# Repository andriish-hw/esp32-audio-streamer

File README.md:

# Dual-ESP32 Modular Audio Streamer

A custom desktop audio streamer featuring a **dual-ESP32 architecture** designed for high reliability, dedicated audio processing, and low-latency hardware control.

---

## 🛠 System Architecture

The project splits functionality across two ESP32 microcontrollers to ensure stability and clean resource allocation:

1. **Main Controller & Bluetooth Receiver (Custom Firmware in `firmware/`):**
   * Implements high-quality Bluetooth A2DP audio sink based on the [esp32-a2dp-sink] with extra codecs (https://github.com/cfint/esp32-a2dp-sink/tree/v5.1) architecture.
   * Handles user controls, audio routing, and display output.
   * Uses the ESP32 hardware **Pulse Counter (PCNT)** peripheral for responsive, zero-lag rotary encoder handling without polling overhead.

2. **Dedicated Web-Radio Module:**
   * Powered by a secondary ESP32 running the proven [Ka-Radio32](https://github.com/karawin/Ka-Radio32) firmware as a dedicated network audio source.
   * Offloads Wi-Fi streaming, network stack management, and web-stream decoding to prevent buffer underruns and core exhaustion on the main system.
   * Communicates with main controller using UART commands.

---

## ⚡ Key Hardware & Firmware Features

* **Digital Audio Routing:** High-resolution I2S output directly to external DAC/amplifier stages.
* **Modular Hardware (KiCad):**
  * Custom mainboard with power management and signal routing.
  * Dedicated front-panel control and display breakout boards.
  * Audio level meter module.
* **Hardware-Accelerated Input:** Native hardware counter (PCNT) integration for smooth volume/menu navigation.
* **Custom Character Handling:** Custom C/C++ routines for Cyrillic metadata decoding and clean display rendering.

---

## 📁 Repository Structure

```text
├── firmware/         # Custom ESP-IDF / C++ firmware for the primary ESP32
├── hardware/         # KiCad schematics, PCB layouts, and component footprints
└── docs/             # Hardware documentation, block diagrams, and photos
---
*Note: The hardware is currently in final assembly and enclosure integration. Full schematic exports (PDF) and device photos will be added.*

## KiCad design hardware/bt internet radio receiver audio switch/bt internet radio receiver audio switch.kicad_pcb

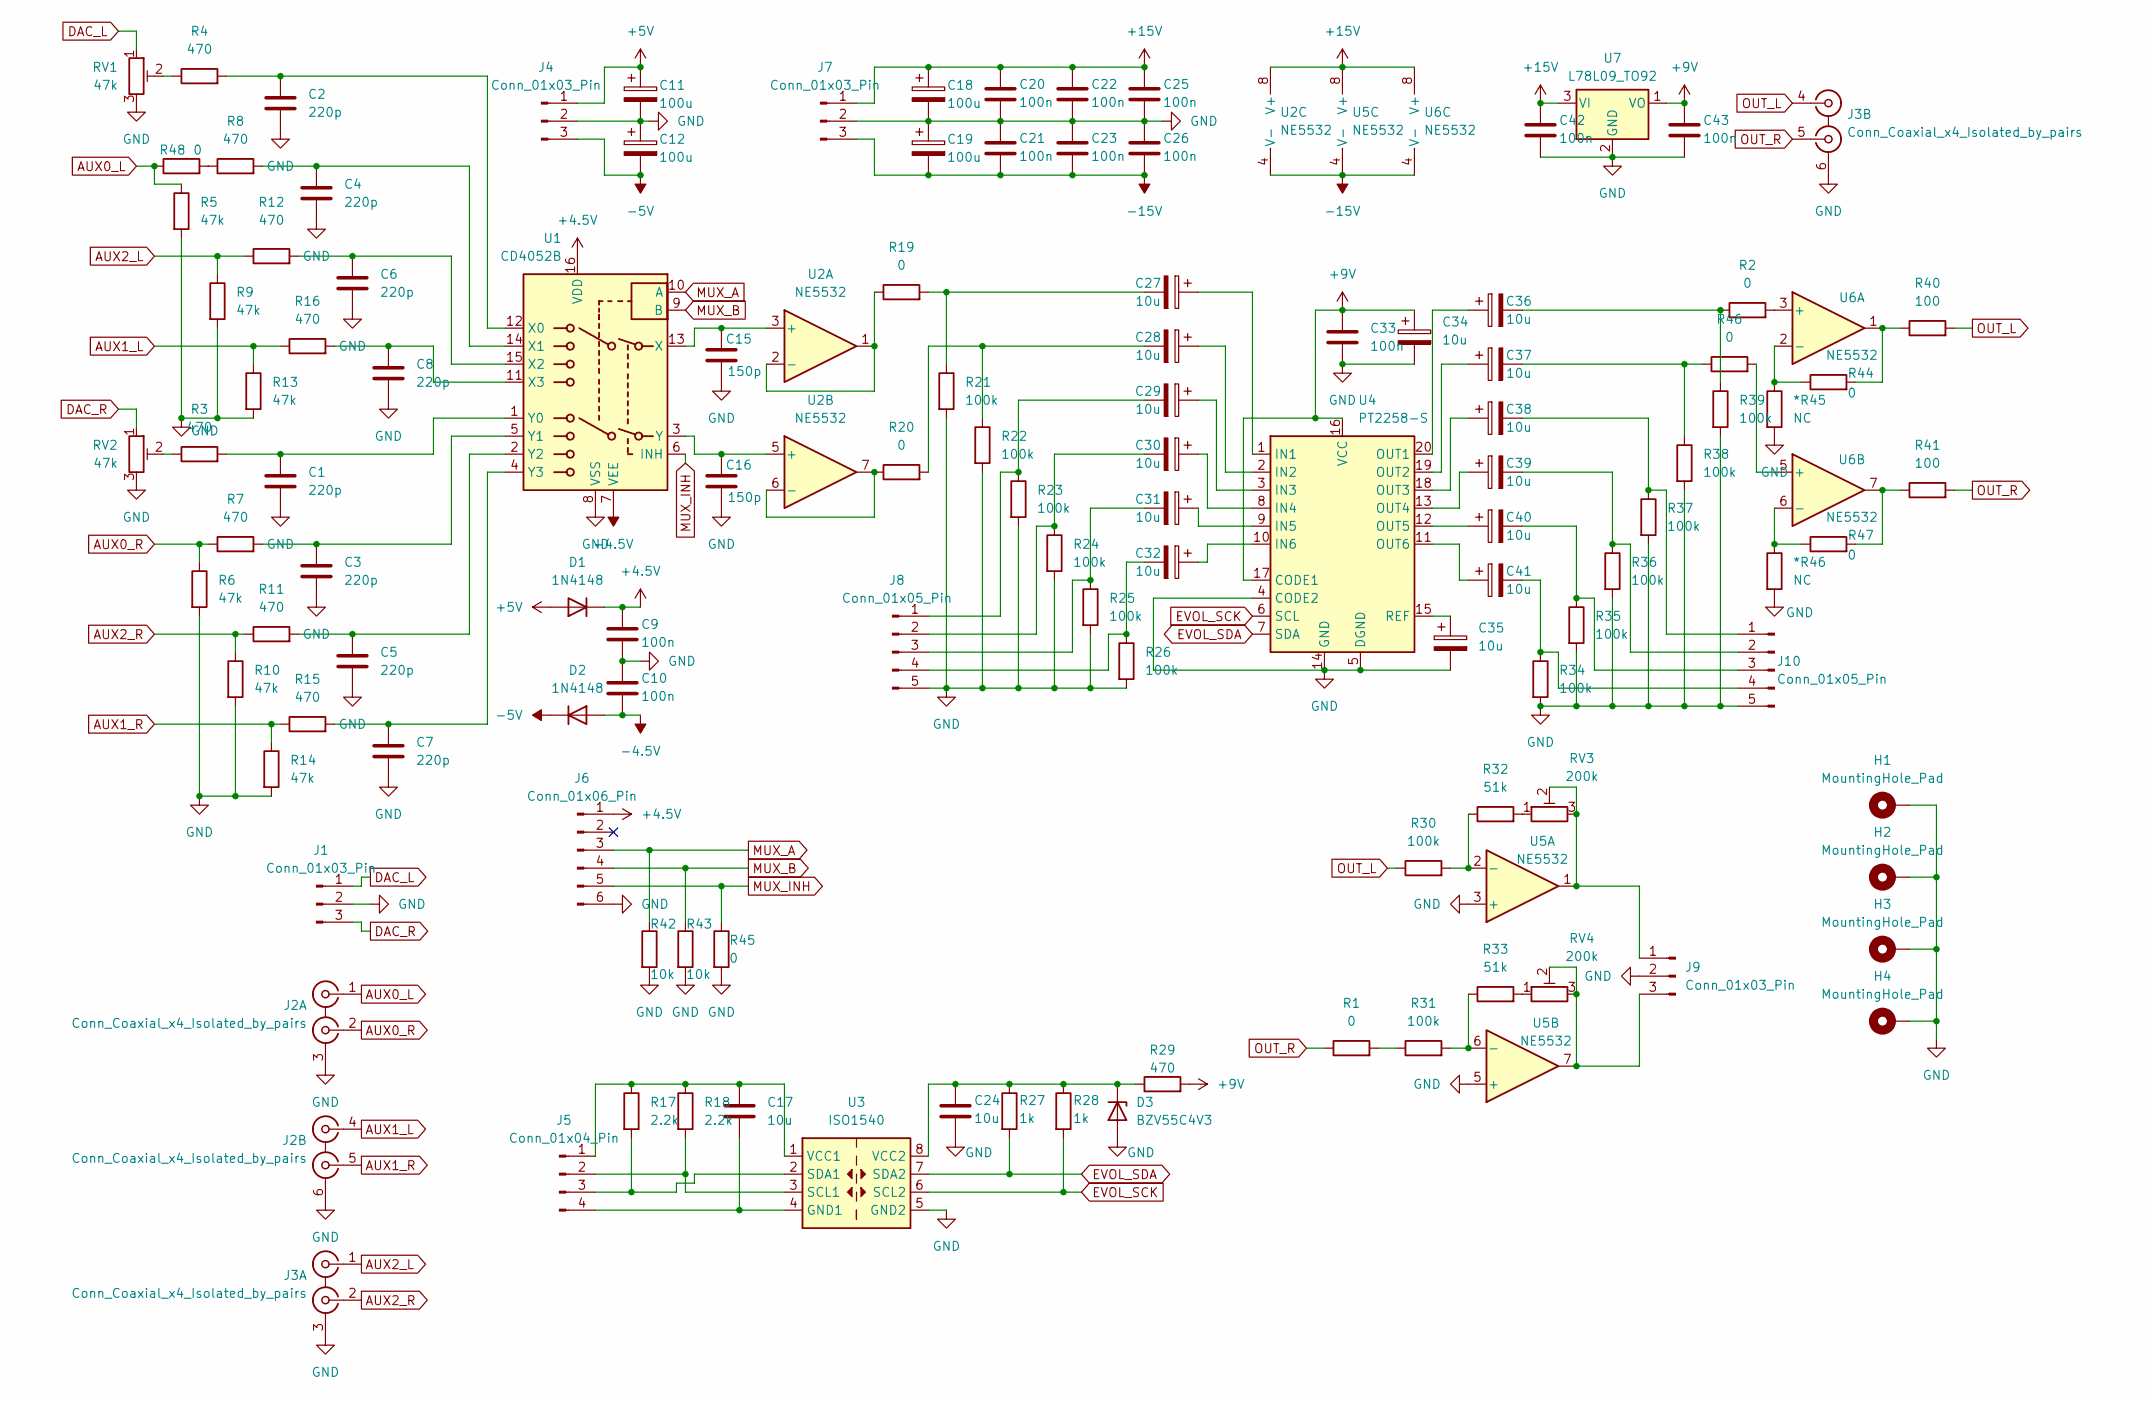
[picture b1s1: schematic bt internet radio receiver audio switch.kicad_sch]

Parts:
*R45, *R46: NC; R_0805_2012Metric_Pad1.20x1.40mm_HandSolder
C1, C2, C3, C4, C5, C6, C7, C8: 220p; C_0805_2012Metric_Pad1.18x1.45mm_HandSolder
C9, C10, C20, C21, C22, C23, C25, C26, C33, C42, C43: 100n; C_0805_2012Metric_Pad1.18x1.45mm_HandSolder
C11, C12, C18, C19: 100u; CP_Radial_D6.3mm_P2.50mm
C15, C16: 150p; C_0805_2012Metric_Pad1.18x1.45mm_HandSolder
C17, C24: 10u; C_1206_3216Metric_Pad1.33x1.80mm_HandSolder
C27, C28, C29, C30, C31, C32, C34, C35, C36, C37, C38, C39, C40, C41: 10u; CP_Radial_D5.0mm_P2.00mm
D1, D2: 1N4148; D_SOD-323_HandSoldering
D3: BZV55C4V3; D_MiniMELF
H1, H2, H3, H4: MountingHole_Pad; MountingHole_3.2mm_M3_DIN965_Pad_TopBottom
J1, J4, J7, J9: Conn_01x03_Pin; PinHeader_1x03_P2.54mm_Vertical
J2, J3: Conn_Coaxial_x4_Isolated_by_pairs; KLS1-RCA-410
J5: Conn_01x04_Pin; PinHeader_1x04_P2.54mm_Vertical
J6: Conn_01x06_Pin; PinHeader_1x06_P2.54mm_Vertical
J8, J10: Conn_01x05_Pin; PinHeader_1x05_P2.54mm_Vertical
R1, R19, R20, R44, R45, R47, R48: 0; R_0805_2012Metric_Pad1.20x1.40mm_HandSolder
R2, R46: 0; R_1206_3216Metric_Pad1.30x1.75mm_HandSolder
R3, R4, R7, R8, R11, R12, R15, R16: 470; R_0805_2012Metric_Pad1.20x1.40mm_HandSolder
R5, R6, R9, R10, R13, R14: 47k; R_0805_2012Metric_Pad1.20x1.40mm_HandSolder
R17, R18: 2.2k; R_0805_2012Metric_Pad1.20x1.40mm_HandSolder
R21, R22, R23, R24, R25, R26, R30, R31, R34, R35, R36, R37, R38, R39: 100k; R_0805_2012Metric_Pad1.20x1.40mm_HandSolder
R27, R28: 1k; R_0805_2012Metric_Pad1.20x1.40mm_HandSolder
R29: 470; R_1206_3216Metric_Pad1.30x1.75mm_HandSolder
R32, R33: 51k; R_0805_2012Metric_Pad1.20x1.40mm_HandSolder
R40, R41: 100; R_0805_2012Metric_Pad1.20x1.40mm_HandSolder
R42, R43: 10k; R_0805_2012Metric_Pad1.20x1.40mm_HandSolder
RV1, RV2: 47k; Potentiometer_Runtron_RM-065_Vertical
RV3, RV4: 200k; Potentiometer_Runtron_RM-065_Vertical
U1: CD4052B; SOIC-16_3.9x9.9mm_P1.27mm
U2, U5, U6: NE5532; DIP-8_W7.62mm_Socket_LongPads
U3: ISO1540; SOIC-8_3.9x4.9mm_P1.27mm
U4: PT2258-S; SO-20_12.8x7.5mm_P1.27mm
U7: L78L09_TO92; TO-92_Inline_Wide

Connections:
+4.5V: C9.1, D1.1 (K), J6.1, U1.16 (VDD)
+5V: C11.1, D1.2 (A), J4.1
+9V: C33.1, C34.1, C43.1, R29.2, U4.16 (VCC), U4.17 (CODE1), U7.1 (VO)
+15V: C18.1, C20.1, C22.1, C25.1, C42.1, J7.1, U2.8 (V+), U5.8 (V+), U6.8 (V+), U7.3 (VI)
-4.5V: C10.2, D2.2 (A), U1.7 (VEE)
-5V: C12.2, D2.1 (K), J4.3
-15V: C19.2, C21.2, C23.2, C26.2, J7.3, U2.4 (V-), U5.4 (V-), U6.4 (V-)
AUX0_L: J2.1 (IN1), R5.1, R48.1
AUX0_R: J2.2 (IN2), R6.1, R7.1
AUX1_L: J2.4 (IN1), R13.1, R16.1
AUX1_R: J2.5 (IN2), R14.1, R15.1
AUX2_L: J3.1 (IN1), R9.1, R12.1
AUX2_R: J3.2 (IN2), R10.1, R11.1
DAC_L: J1.1, RV1.1
DAC_R: J1.3, RV2.1
EVOL_SCK: R28.2, U3.6 (SCL2), U4.6 (SCL)
EVOL_SDA: R27.2, U3.7 (SDA2), U4.7 (SDA)
GND: *R45.2, *R46.2, C1.2, C2.2, C3.2, C4.2, C5.2, C6.2, C7.2, C8.2, C9.2, C10.1, C11.2, C12.1, C15.2, C16.2, C18.2, C19.1, C20.2, C21.1, C22.2, C23.1, C24.2, C25.2, C26.1, C33.2, C34.2, C35.2, C42.2, C43.2, D3.2 (A), H1.1, H2.1, H3.1, H4.1, J1.2, J2.3 (EXT), J2.6 (EXT), J3.3 (EXT), J3.6 (EXT), J4.2, J6.6, J7.2, J8.5, J9.2, J10.5, R5.2, R6.2, R9.2, R10.2, R13.2, R14.2, R21.2, R22.2, R23.2, R24.2, R25.2, R26.2, R34.2, R35.2, R36.2, R37.2, R38.2, R39.2, R42.2, R43.2, R45.2, RV1.3, RV2.3, U1.8 (VSS), U3.5 (GND2), U4.4 (CODE2), U4.5 (DGND), U4.14 (GND), U5.3 (+), U5.5 (+), U7.2 (GND)
MUX_A: J6.3, R42.1, U1.10 (A)
MUX_B: J6.4, R43.1, U1.9 (B)
MUX_INH: J6.5, R45.1, U1.6 (INH)
unnamed: C27.2, R19.2, R21.1
unnamed: C28.2, R20.2, R22.1
unnamed: C36.2, R2.1, R39.1
unnamed: C37.2, R38.1, R46.1
unnamed: C24.1, D3.1 (K), R27.1, R28.1, R29.1, U3.8 (VCC2)
unnamed: C17.1, J5.1, R17.1, R18.1, U3.1 (VCC1)
unnamed: J5.2, R18.2, U3.3 (SCL1)
unnamed: J5.3, R17.2, U3.2 (SDA1)
unnamed: C17.2, J5.4, U3.4 (GND1)
unnamed: C29.2, J8.1, R23.1
unnamed: C30.2, J8.2, R24.1
unnamed: C31.2, J8.3, R25.1
unnamed: C32.2, J8.4, R26.1
unnamed: J9.1, RV3.2, RV3.3, U5.1
unnamed: J9.3, RV4.2, RV4.3, U5.7
unnamed: C38.2, J10.1, R37.1
unnamed: C39.2, J10.2, R36.1
unnamed: C40.2, J10.3, R35.1
unnamed: C41.2, J10.4, R34.1
unnamed: R1.2, R31.1
unnamed: R3.1, RV2.2
unnamed: R4.1, RV1.2
unnamed: R32.2, RV3.1
unnamed: R33.2, RV4.1
unnamed: R40.1, R44.2, U6.1
unnamed: R41.1, R47.2, U6.7
unnamed: R8.1, R48.2
unnamed: C2.1, R4.2, U1.12 (X0)
unnamed: C4.1, R8.2, U1.14 (X1)
unnamed: C6.1, R12.2, U1.15 (X2)
unnamed: C8.1, R16.2, U1.11 (X3)
unnamed: C15.1, U1.13 (X), U2.3 (+)
unnamed: C1.1, R3.2, U1.1 (Y0)
unnamed: C3.1, R7.2, U1.5 (Y1)
unnamed: C5.1, R11.2, U1.2 (Y2)
unnamed: C7.1, R15.2, U1.4 (Y3)
unnamed: C16.1, U1.3 (Y), U2.5 (+)
unnamed: R19.1, U2.1, U2.2 (-)
unnamed: R20.1, U2.6 (-), U2.7
unnamed: C27.1, U4.1 (IN1)
unnamed: C28.1, U4.2 (IN2)
unnamed: C29.1, U4.3 (IN3)
unnamed: C30.1, U4.8 (IN4)
unnamed: C31.1, U4.9 (IN5)
unnamed: C32.1, U4.10 (IN6)
unnamed: C36.1, U4.20 (OUT1)
unnamed: C37.1, U4.19 (OUT2)
unnamed: C38.1, U4.18 (OUT3)
unnamed: C39.1, U4.13 (OUT4)
unnamed: C40.1, U4.12 (OUT5)
unnamed: C41.1, U4.11 (OUT6)
unnamed: C35.1, U4.15 (REF)
unnamed: R30.2, R32.1, U5.2 (-)
unnamed: R31.2, R33.1, U5.6 (-)
unnamed: R2.2, U6.3 (+)
unnamed: *R45.1, R44.1, U6.2 (-)
unnamed: R46.2, U6.5 (+)
unnamed: *R46.1, R47.1, U6.6 (-)
OUT_L: J3.4 (IN1), R30.1, R40.2
OUT_R: J3.5 (IN2), R1.1, R41.2

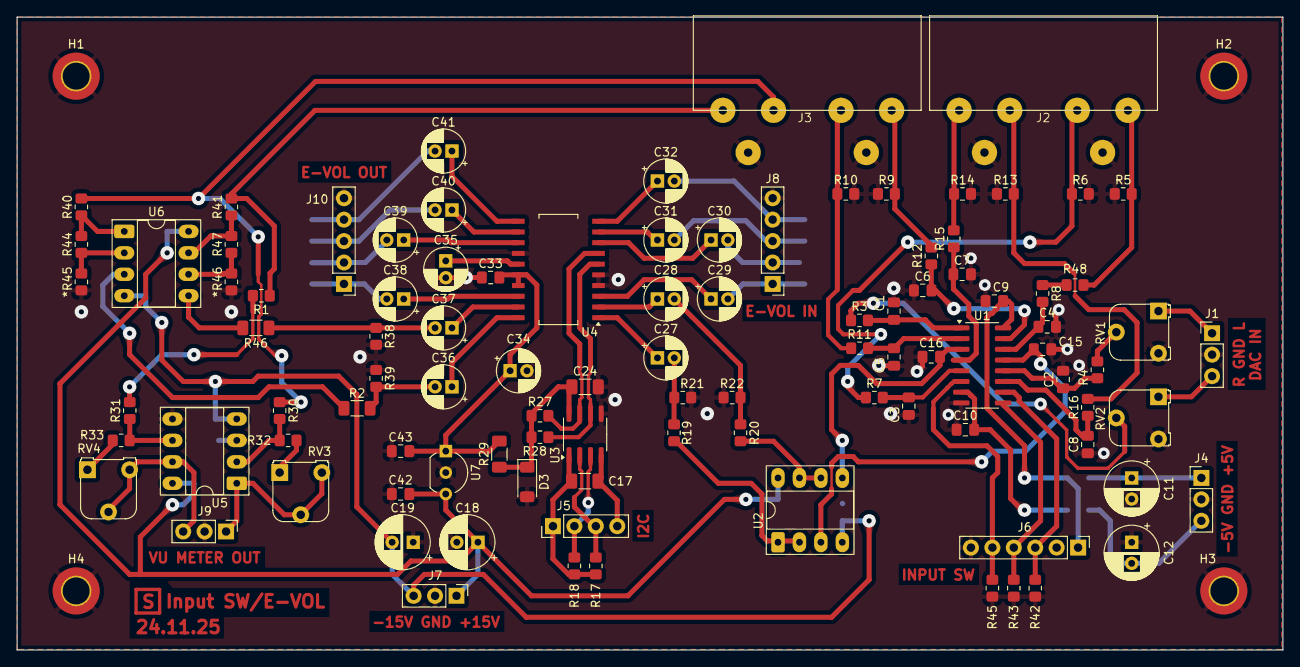
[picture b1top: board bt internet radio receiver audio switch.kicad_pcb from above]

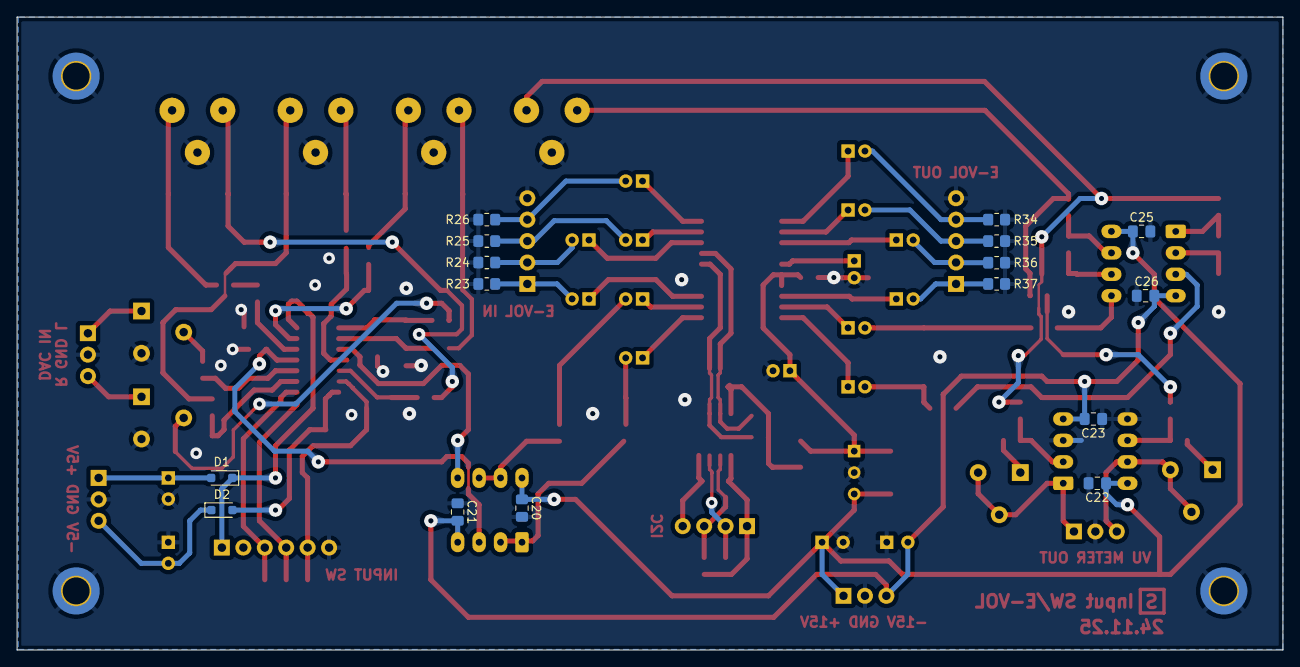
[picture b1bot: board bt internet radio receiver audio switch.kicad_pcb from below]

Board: 2 copper layers, 150.0 x 75.0 mm, 119 parts (16 on the bottom side), 81 nets.

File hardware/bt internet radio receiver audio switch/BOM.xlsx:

Reference | Qty | Value | DNP | Exclude from BOM | Exclude from Board | Footprint | Datasheet
*R45,*R46 | 2 | NC | 1 |  |  | Resistor_SMD:R_0805_2012Metric_Pad1.20x1.40mm_HandSolder | ~
C1,C2,C3,C4,C5,C6,C7,C8 | 8 | 220p | 1 |  |  | Capacitor_SMD:C_0805_2012Metric_Pad1.18x1.45mm_HandSolder | ~
C9,C10,C20,C21,C22,C23,C25,C26,C33,C42,C43 | 11 | 100n | 0 |  |  | Capacitor_SMD:C_0805_2012Metric_Pad1.18x1.45mm_HandSolder | ~
C11,C12,C18,C19 | 4 | 100u | 0 |  |  | Capacitor_THT:CP_Radial_D6.3mm_P2.50mm | ~
C15,C16 | 2 | 150p | 1 |  |  | Capacitor_SMD:C_0805_2012Metric_Pad1.18x1.45mm_HandSolder | ~
C17,C24 | 2 | 10u | 0 |  |  | Capacitor_SMD:C_1206_3216Metric_Pad1.33x1.80mm_HandSolder | ~
C27,C28,C29,C30,C31,C32,C34,C35,C36,C37,C38,C39,C40,C41 | 14 | 10u | 0 |  |  | Capacitor_THT:CP_Radial_D5.0mm_P2.00mm | ~
D1,D2 | 2 | 1N4148 | 0 |  |  | Diode_SMD:D_SOD-323_HandSoldering | https://assets.nexperia.com/documents/data-sheet/1N4148_1N4448.pdf
D3 | 1 | BZV55C4V3 | 1 |  |  | Diode_SMD:D_MiniMELF | https://assets.nexperia.com/documents/data-sheet/BZV55_SER.pdf
J1,J4,J7,J9 | 4 | Conn_01x03_Pin | 0 |  |  | Connector_PinHeader_2.54mm:PinHeader_1x03_P2.54mm_Vertical | ~
J2,J3 | 2 | Conn_Coaxial_x4_Isolated_by_pairs | 0 |  |  | Connector:KLS1-RCA-410
J5 | 1 | Conn_01x04_Pin | 0 |  |  | Connector_PinHeader_2.54mm:PinHeader_1x04_P2.54mm_Vertical | ~
J6 | 1 | Conn_01x06_Pin | 0 |  |  | Connector_PinHeader_2.54mm:PinHeader_1x06_P2.54mm_Vertical | ~
J8,J10 | 2 | Conn_01x05_Pin | 0 |  |  | Connector_PinHeader_2.54mm:PinHeader_1x05_P2.54mm_Vertical | ~
R1,R19,R20,R44,R45,R47 | 6 | 0 | 1 |  |  | Resistor_SMD:R_0805_2012Metric_Pad1.20x1.40mm_HandSolder | ~
R2,R46 | 2 | 0 | 1 |  |  | Resistor_SMD:R_1206_3216Metric_Pad1.30x1.75mm_HandSolder | ~
R3,R4,R7,R8,R11,R12,R15,R16 | 8 | 470 | 1 |  |  | Resistor_SMD:R_0805_2012Metric_Pad1.20x1.40mm_HandSolder | ~
R5,R6,R9,R10,R13,R14 | 6 | 47k | 1 |  |  | Resistor_SMD:R_0805_2012Metric_Pad1.20x1.40mm_HandSolder | ~
R17,R18 | 2 | 2.2k | 0 |  |  | Resistor_SMD:R_0805_2012Metric_Pad1.20x1.40mm_HandSolder | ~
R21,R22,R23,R24,R25,R26,R30,R31,R34,R35,R36,R37,R38,R39 | 14 | 100k | 0 |  |  | Resistor_SMD:R_0805_2012Metric_Pad1.20x1.40mm_HandSolder | ~
R27,R28 | 2 | 1k | 0 |  |  | Resistor_SMD:R_0805_2012Metric_Pad1.20x1.40mm_HandSolder | ~
R29 | 1 | 470 | 1 |  |  | Resistor_SMD:R_1206_3216Metric_Pad1.30x1.75mm_HandSolder | ~
R32,R33 | 2 | 51k | 0 |  |  | Resistor_SMD:R_0805_2012Metric_Pad1.20x1.40mm_HandSolder | ~
R40,R41 | 2 | 100 | 1 |  |  | Resistor_SMD:R_0805_2012Metric_Pad1.20x1.40mm_HandSolder | ~
R42,R43 | 2 | 10k | 1 |  |  | Resistor_SMD:R_0805_2012Metric_Pad1.20x1.40mm_HandSolder | ~
RV1,RV2 | 2 | 47k | 0 |  |  | Potentiometer_THT:Potentiometer_Runtron_RM-065_Vertical | ~
RV3,RV4 | 2 | 200k | 0 |  |  | Potentiometer_THT:Potentiometer_Runtron_RM-065_Vertical | ~
U1 | 1 | CD4052B | 1 |  |  | Package_SO:SOIC-16_3.9x9.9mm_P1.27mm | http://www.ti.com/lit/ds/symlink/cd4052b.pdf
U2,U5,U6 | 3 | NE5532 | 0 |  |  | Package_DIP:DIP-8_W7.62mm_Socket_LongPads | http://www.ti.com/lit/ds/symlink/ne5532.pdf
U3 | 1 | ISO1540 | 0 |  |  | Package_SO:SOIC-8_3.9x4.9mm_P1.27mm | http://www.ti.com/lit/ds/symlink/iso1541.pdf
U4 | 1 | PT2258-S | 0 |  |  | Package_SO:SO-20_12.8x7.5mm_P1.27mm | http://www.princeton.com.tw/Portals/0/Product/PT2258-s.pdf
U7 | 1 | L78L09_TO92 | 0 |  |  | Package_TO_SOT_THT:TO-92_Inline_Wide | http://www.st.com/content/ccc/resource/technical/document/da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
 | 114
 | 41 | 0.35964912280701755

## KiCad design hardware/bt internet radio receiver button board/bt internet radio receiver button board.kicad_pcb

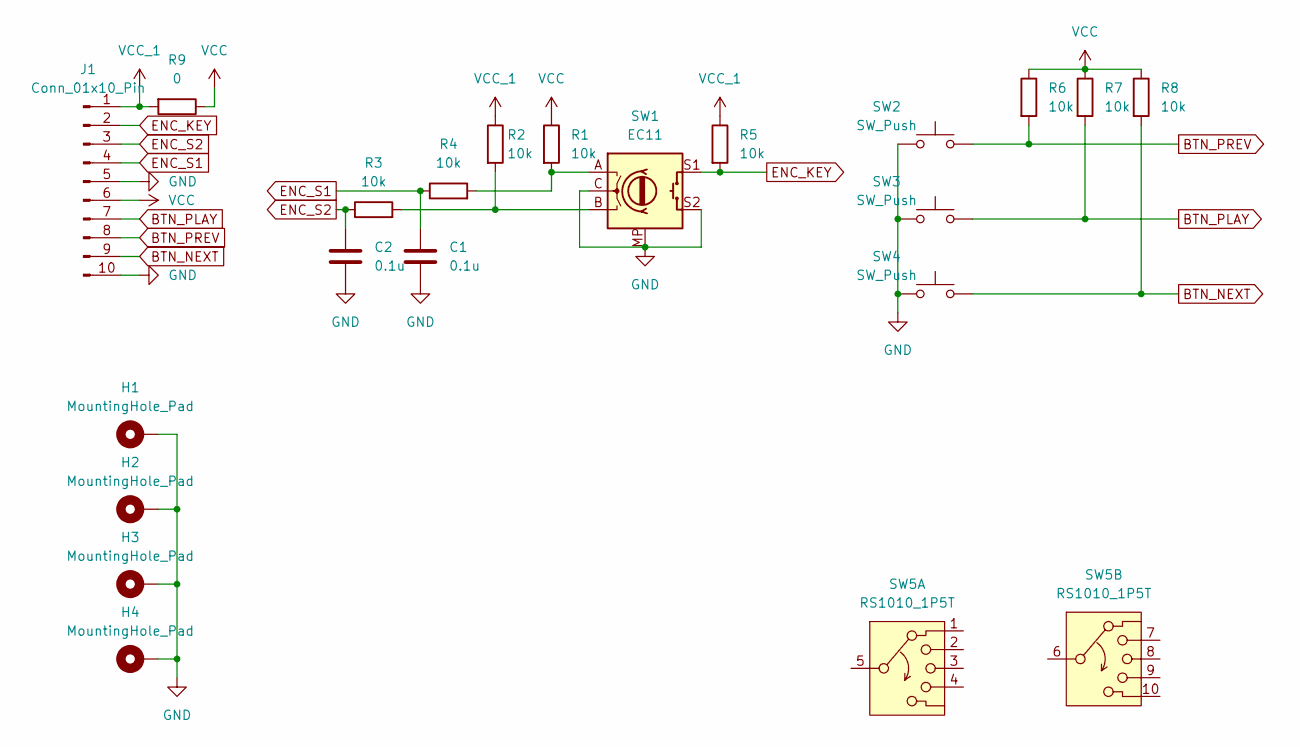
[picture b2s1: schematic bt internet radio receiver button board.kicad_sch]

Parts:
C1, C2: 0.1u; C_0805_2012Metric_Pad1.18x1.45mm_HandSolder
H1, H2, H3, H4: MountingHole_Pad; MountingHole_3.2mm_M3_Pad_TopBottom
J1: Conn_01x10_Pin; PinHeader_1x10_P2.54mm_Horizontal
R1, R2, R3, R4, R5, R6, R7, R8: 10k; R_0805_2012Metric_Pad1.20x1.40mm_HandSolder
R9: 0; R_Axial_DIN0204_L3.6mm_D1.6mm_P7.62mm_Horizontal
SW1: EC11; RotaryEncoder_Alps_EC11E-Switch_Vertical_H20mm
SW2, SW3, SW4: SW_Push; SW_PUSH_6mm
SW5: RS1010_1P5T

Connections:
BTN_NEXT: J1.9, R8.2, SW4.1
BTN_PLAY: J1.7, R7.2, SW3.1
BTN_PREV: J1.8, R6.2, SW2.1
ENC_KEY: J1.2, R5.2, SW1.S1
ENC_S1: C1.1, J1.4, R4.1
ENC_S2: C2.1, J1.3, R3.1
GND: C1.2, C2.2, H1.1, H2.1, H3.1, H4.1, J1.5, J1.10, SW1.C, SW1.MP, SW1.S2, SW2.2, SW3.2, SW4.2
unnamed: R1.2, R4.2, SW1.A
unnamed: R2.2, R3.2, SW1.B
VCC: J1.6, R1.1, R6.1, R7.1, R8.1, R9.1
VCC_1: J1.1, R2.1, R5.1, R9.2

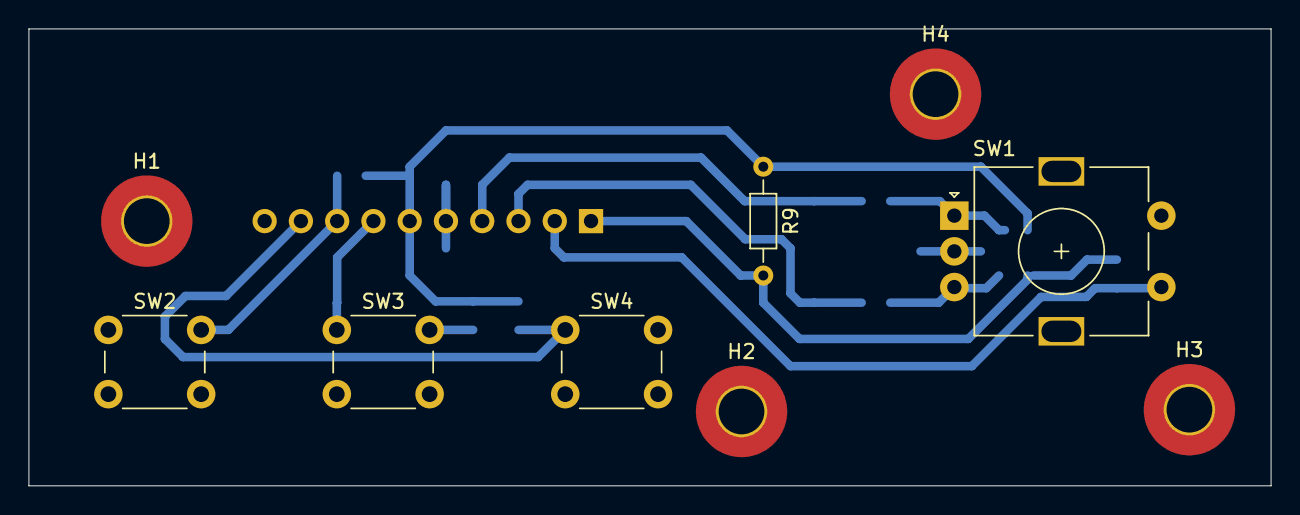
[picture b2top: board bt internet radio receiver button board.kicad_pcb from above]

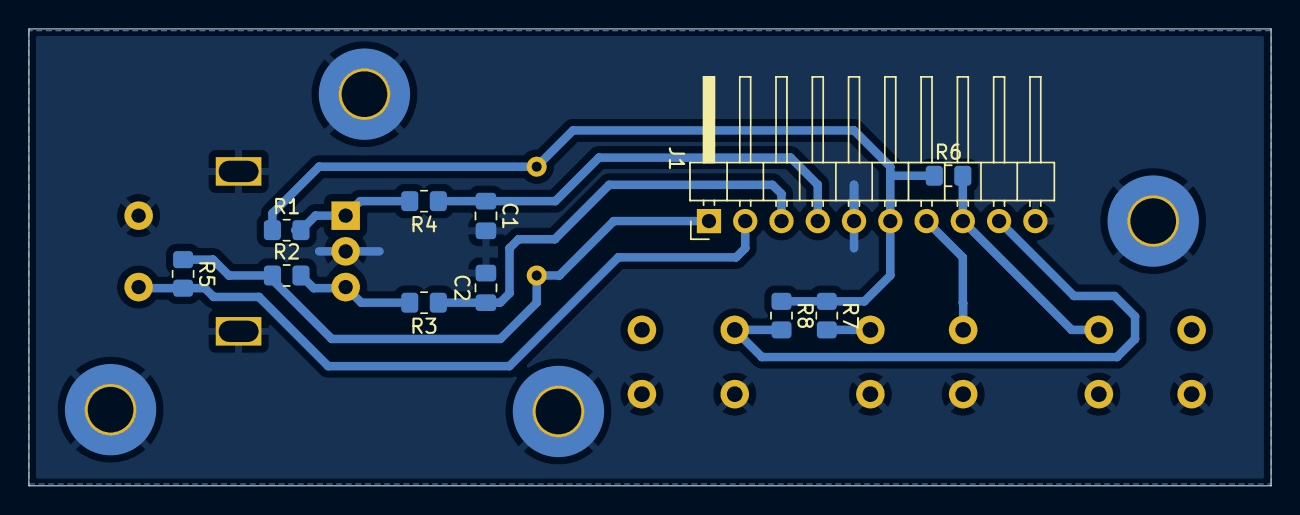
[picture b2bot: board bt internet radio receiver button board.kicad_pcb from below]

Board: 2 copper layers, 87.0 x 32.0 mm, 20 parts (11 on the bottom side), 11 nets.

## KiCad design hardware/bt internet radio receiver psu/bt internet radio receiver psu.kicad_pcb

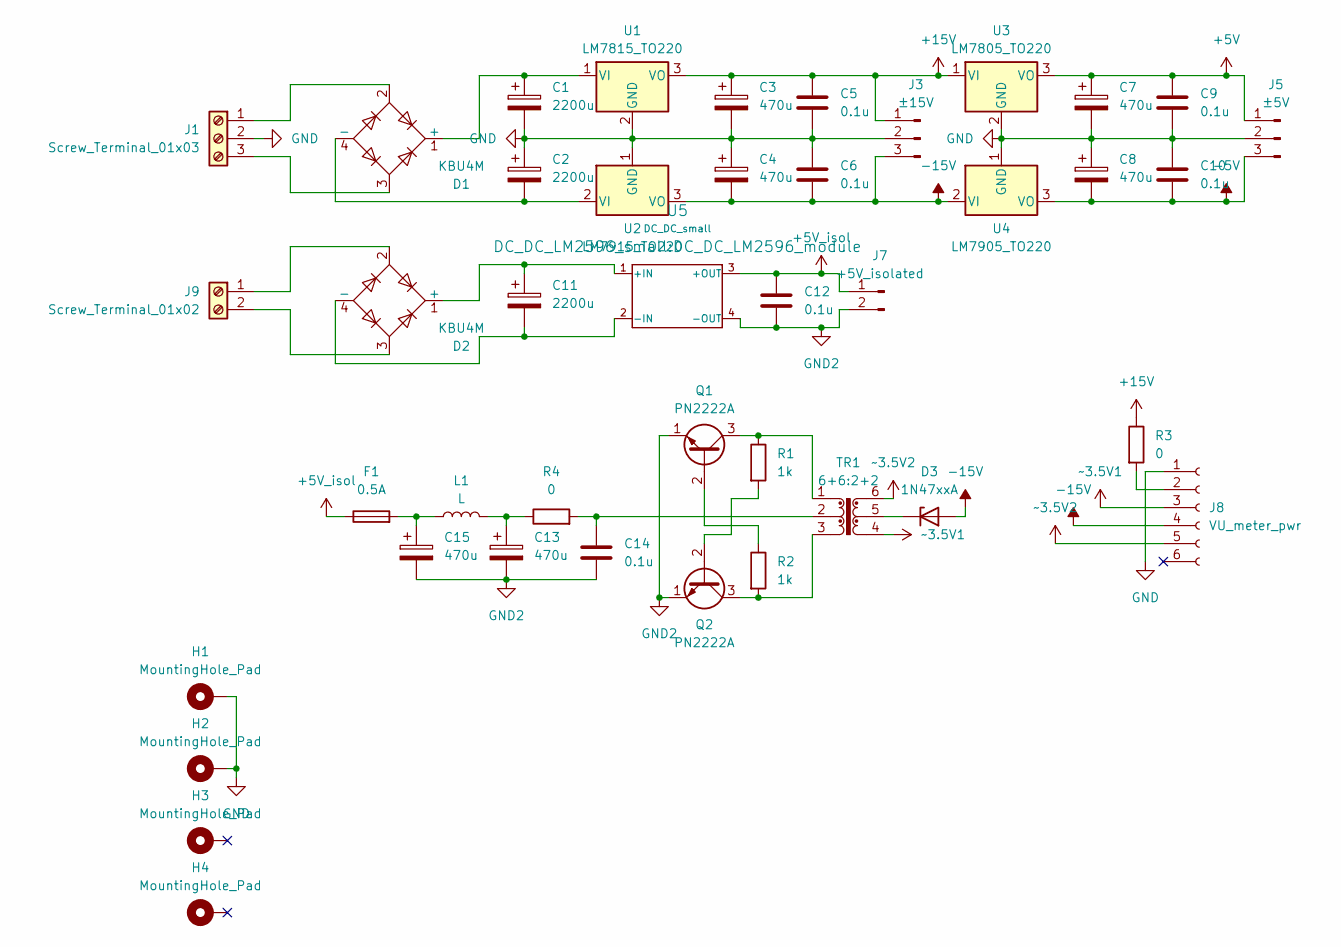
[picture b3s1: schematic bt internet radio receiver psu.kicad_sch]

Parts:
C1, C2, C11: 2200u; C_Radial_D16.0mm_H25.0mm_P7.50mm
C3, C4, C7, C8, C13, C15: 470u; C_Radial_D10.0mm_H12.5mm_P5.00mm
C5, C6, C9, C10, C12, C14: 0.1u; C_Disc_D4.7mm_W2.5mm_P5.00mm
D1, D2: KBU4M; Diode_Bridge_Vishay_KBPM
D3: 1N47xxA; D_DO-41_SOD81_P5.08mm_Vertical_KathodeUp
F1: 0.5A; Fuseholder_Clip-5x20mm_Keystone_3512_Inline_P23.62x7.27mm_D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
H1, H2, H3, H4: MountingHole_Pad; MountingHole_3.2mm_M3_DIN965_Pad_TopOnly
J1: Screw_Terminal_01x03; TerminalBlock_bornier-3_P5.08mm
J3: ±15V; PinHeader_1x03_P2.54mm_Vertical
J5: ±5V; PinHeader_1x03_P2.54mm_Vertical
J7: +5V_isolated; PinHeader_1x02_P2.54mm_Vertical
J8: VU_meter_pwr; PinSocket_1x06_P2.54mm_Vertical
J9: Screw_Terminal_01x02; TerminalBlock_bornier-2_P5.08mm
L1: L; L_Radial_D12.0mm_P6.00mm_Murata_1900R
Q1, Q2: PN2222A; TO-92_Inline_Wide
R1, R2: 1k; R_Axial_DIN0207_L6.3mm_D2.5mm_P10.16mm_Horizontal
R3: 0; R_Axial_DIN0207_L6.3mm_D2.5mm_P10.16mm_Horizontal
R4: 0; R_Axial_DIN0204_L3.6mm_D1.6mm_P7.62mm_Horizontal
TR1: 6+6:2+2; Transformer_Toroid_Tapped_D=23mm_d=13mm
U1: LM7815_TO220; TO-220-3_Vertical
U2: LM7915_TO220; TO-220-3_Vertical
U3: LM7805_TO220; TO-220-3_Vertical
U4: LM7905_TO220; TO-220-3_Vertical
U5: DC_DC_small; DC_DC_LM2596_module

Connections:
+5V: C7.1, C9.1, J5.1, U3.3 (VO)
+5V_isol: C12.1, F1.1, J7.1, U5.3 (+OUT)
+15V: C3.1, C5.1, J3.1, R3.1, U1.3 (VO), U3.1 (VI)
-5V: C8.2, C10.2, J5.3, U4.3 (VO)
-15V: C4.2, C6.2, D3.2 (A), J3.3, J8.4, U2.3 (VO), U4.2 (VI)
GND: C1.2, C2.1, C3.2, C4.1, C5.2, C6.1, C7.2, C8.1, C9.2, C10.1, H1.1, H2.1, J1.2, J3.2, J5.2, J8.1, U1.2 (GND), U2.1 (GND), U3.2 (GND), U4.1 (GND)
GND2: C12.2, C13.2, C14.2, C15.2, J7.2, Q1.1 (E), Q2.1 (E), U5.4 (-OUT)
unnamed: C13.1, L1.2, R4.1
unnamed: C14.1, R4.2, TR1.2
unnamed: C15.1, F1.2, L1.1
unnamed: C1.1, D1.1 (+), U1.1 (VI)
unnamed: C2.2, D1.4 (-), U2.2 (VI)
unnamed: C11.1, D2.1 (+), U5.1 (+IN)
unnamed: C11.2, D2.4 (-), U5.2 (-IN)
unnamed: D3.1 (K), TR1.5
unnamed: D1.2, J1.1
unnamed: D1.3, J1.3
unnamed: J8.2, R3.2
unnamed: D2.2, J9.1
unnamed: D2.3, J9.2
unnamed: Q1.2 (B), R2.1
unnamed: Q1.3 (C), R1.1, TR1.1
unnamed: Q2.2 (B), R1.2
unnamed: Q2.3 (C), R2.2, TR1.3
~3.5V1: J8.3, TR1.4
~3.5V2: J8.5, TR1.6

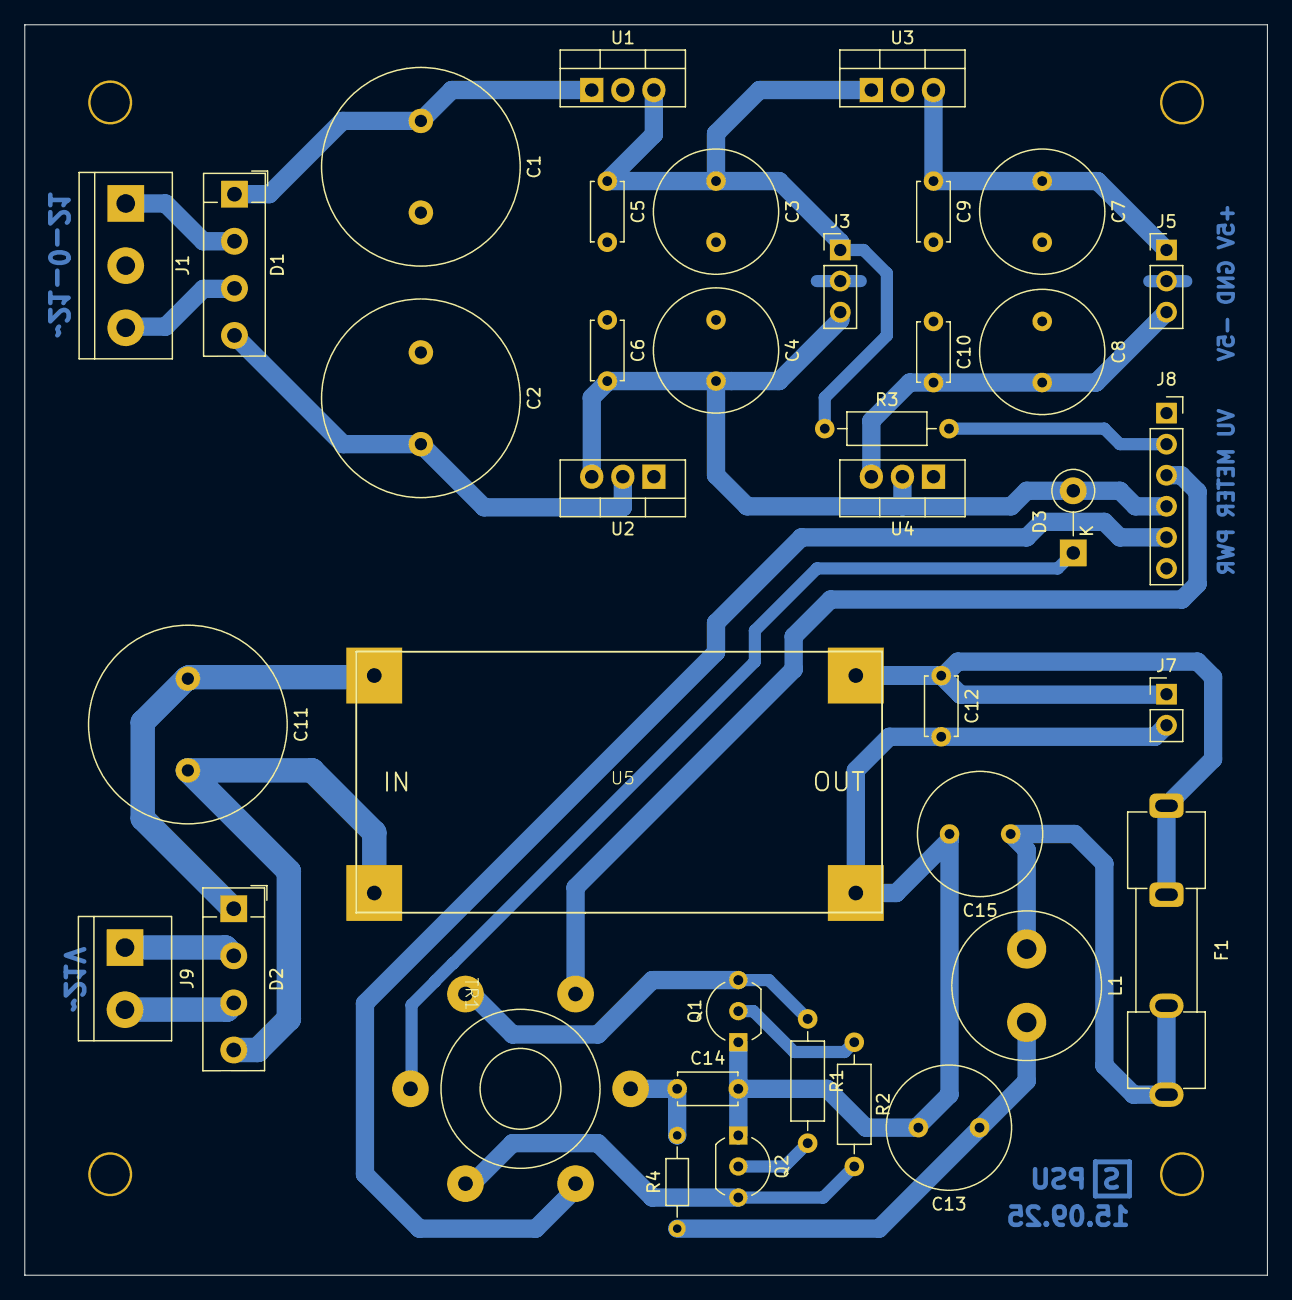
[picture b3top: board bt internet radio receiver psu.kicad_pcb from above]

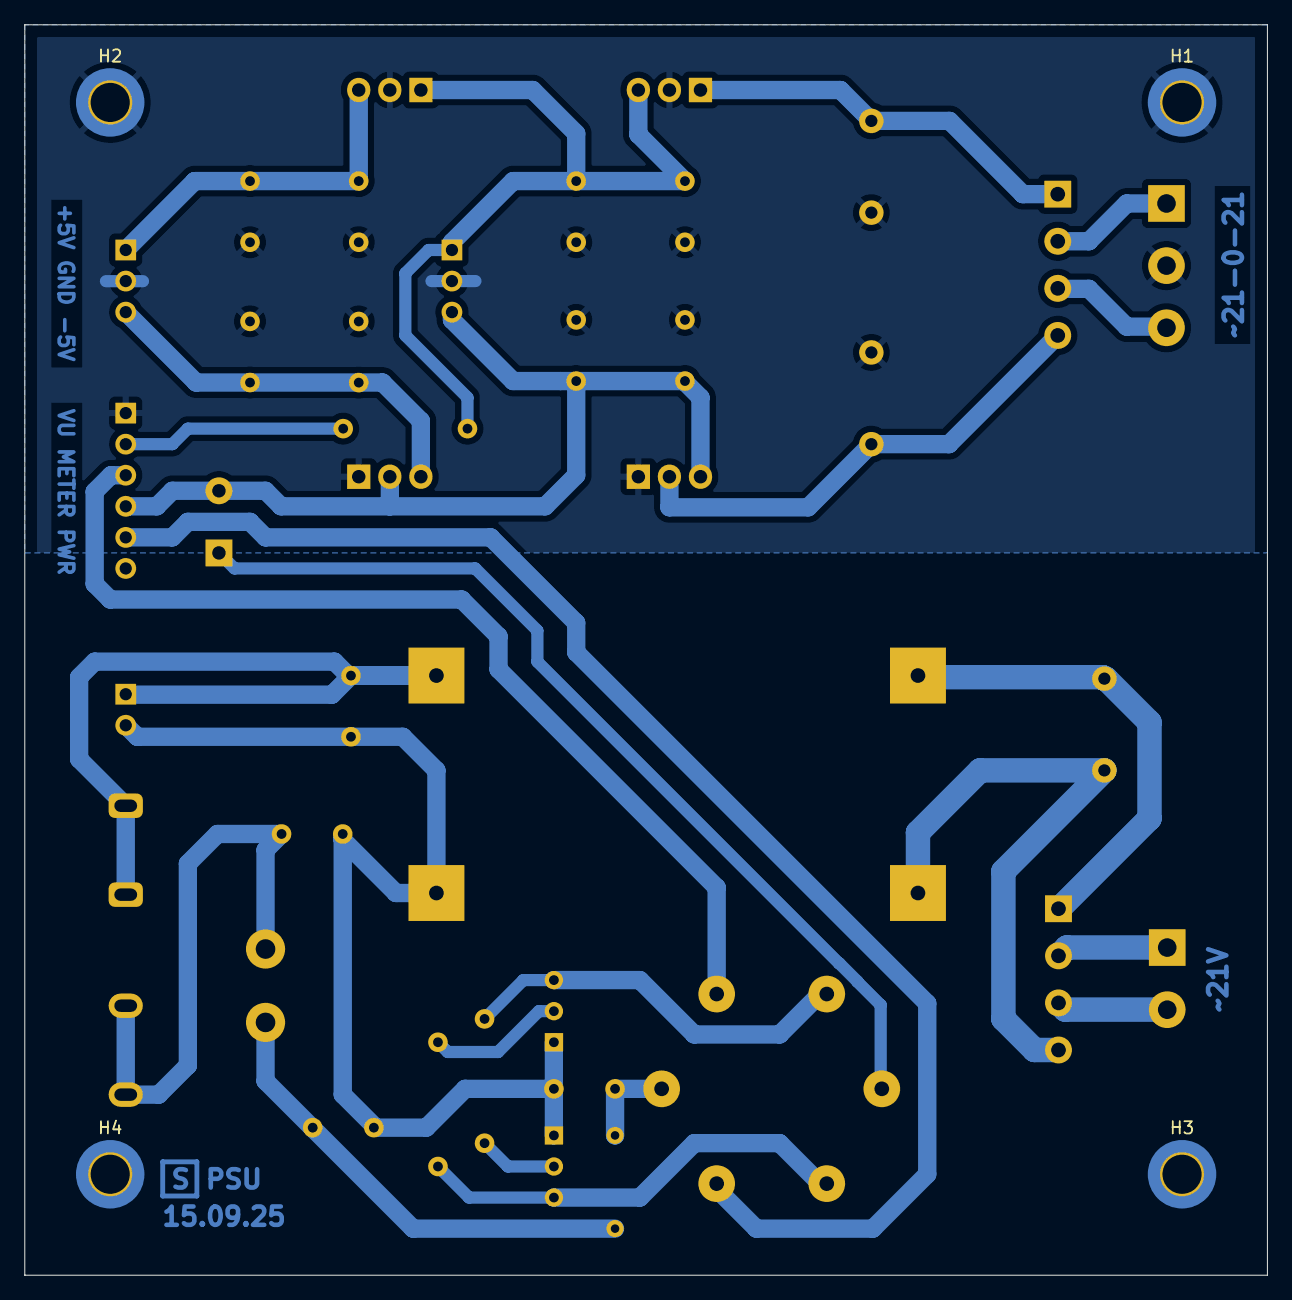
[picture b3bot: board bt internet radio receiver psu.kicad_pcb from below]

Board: 2 copper layers, 101.6 x 102.2 mm, 42 parts (4 on the bottom side), 26 nets.
